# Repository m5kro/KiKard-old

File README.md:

# KiKard-old
KiKard is a non working attempt at creating an NFC testing device. This repo is just here as an example for what not to do.<br>
<br>
There will be a v2 of the project where I fix my mistakes, lower the costs, and make some general improvements.<br>
<br>
Here's a medium article explaining what went wrong: [Here](https://medium.com/the-first-digit/challenges-of-designing-hardware-910d764eaf81)

# Images
Here's what it looks like:<br>

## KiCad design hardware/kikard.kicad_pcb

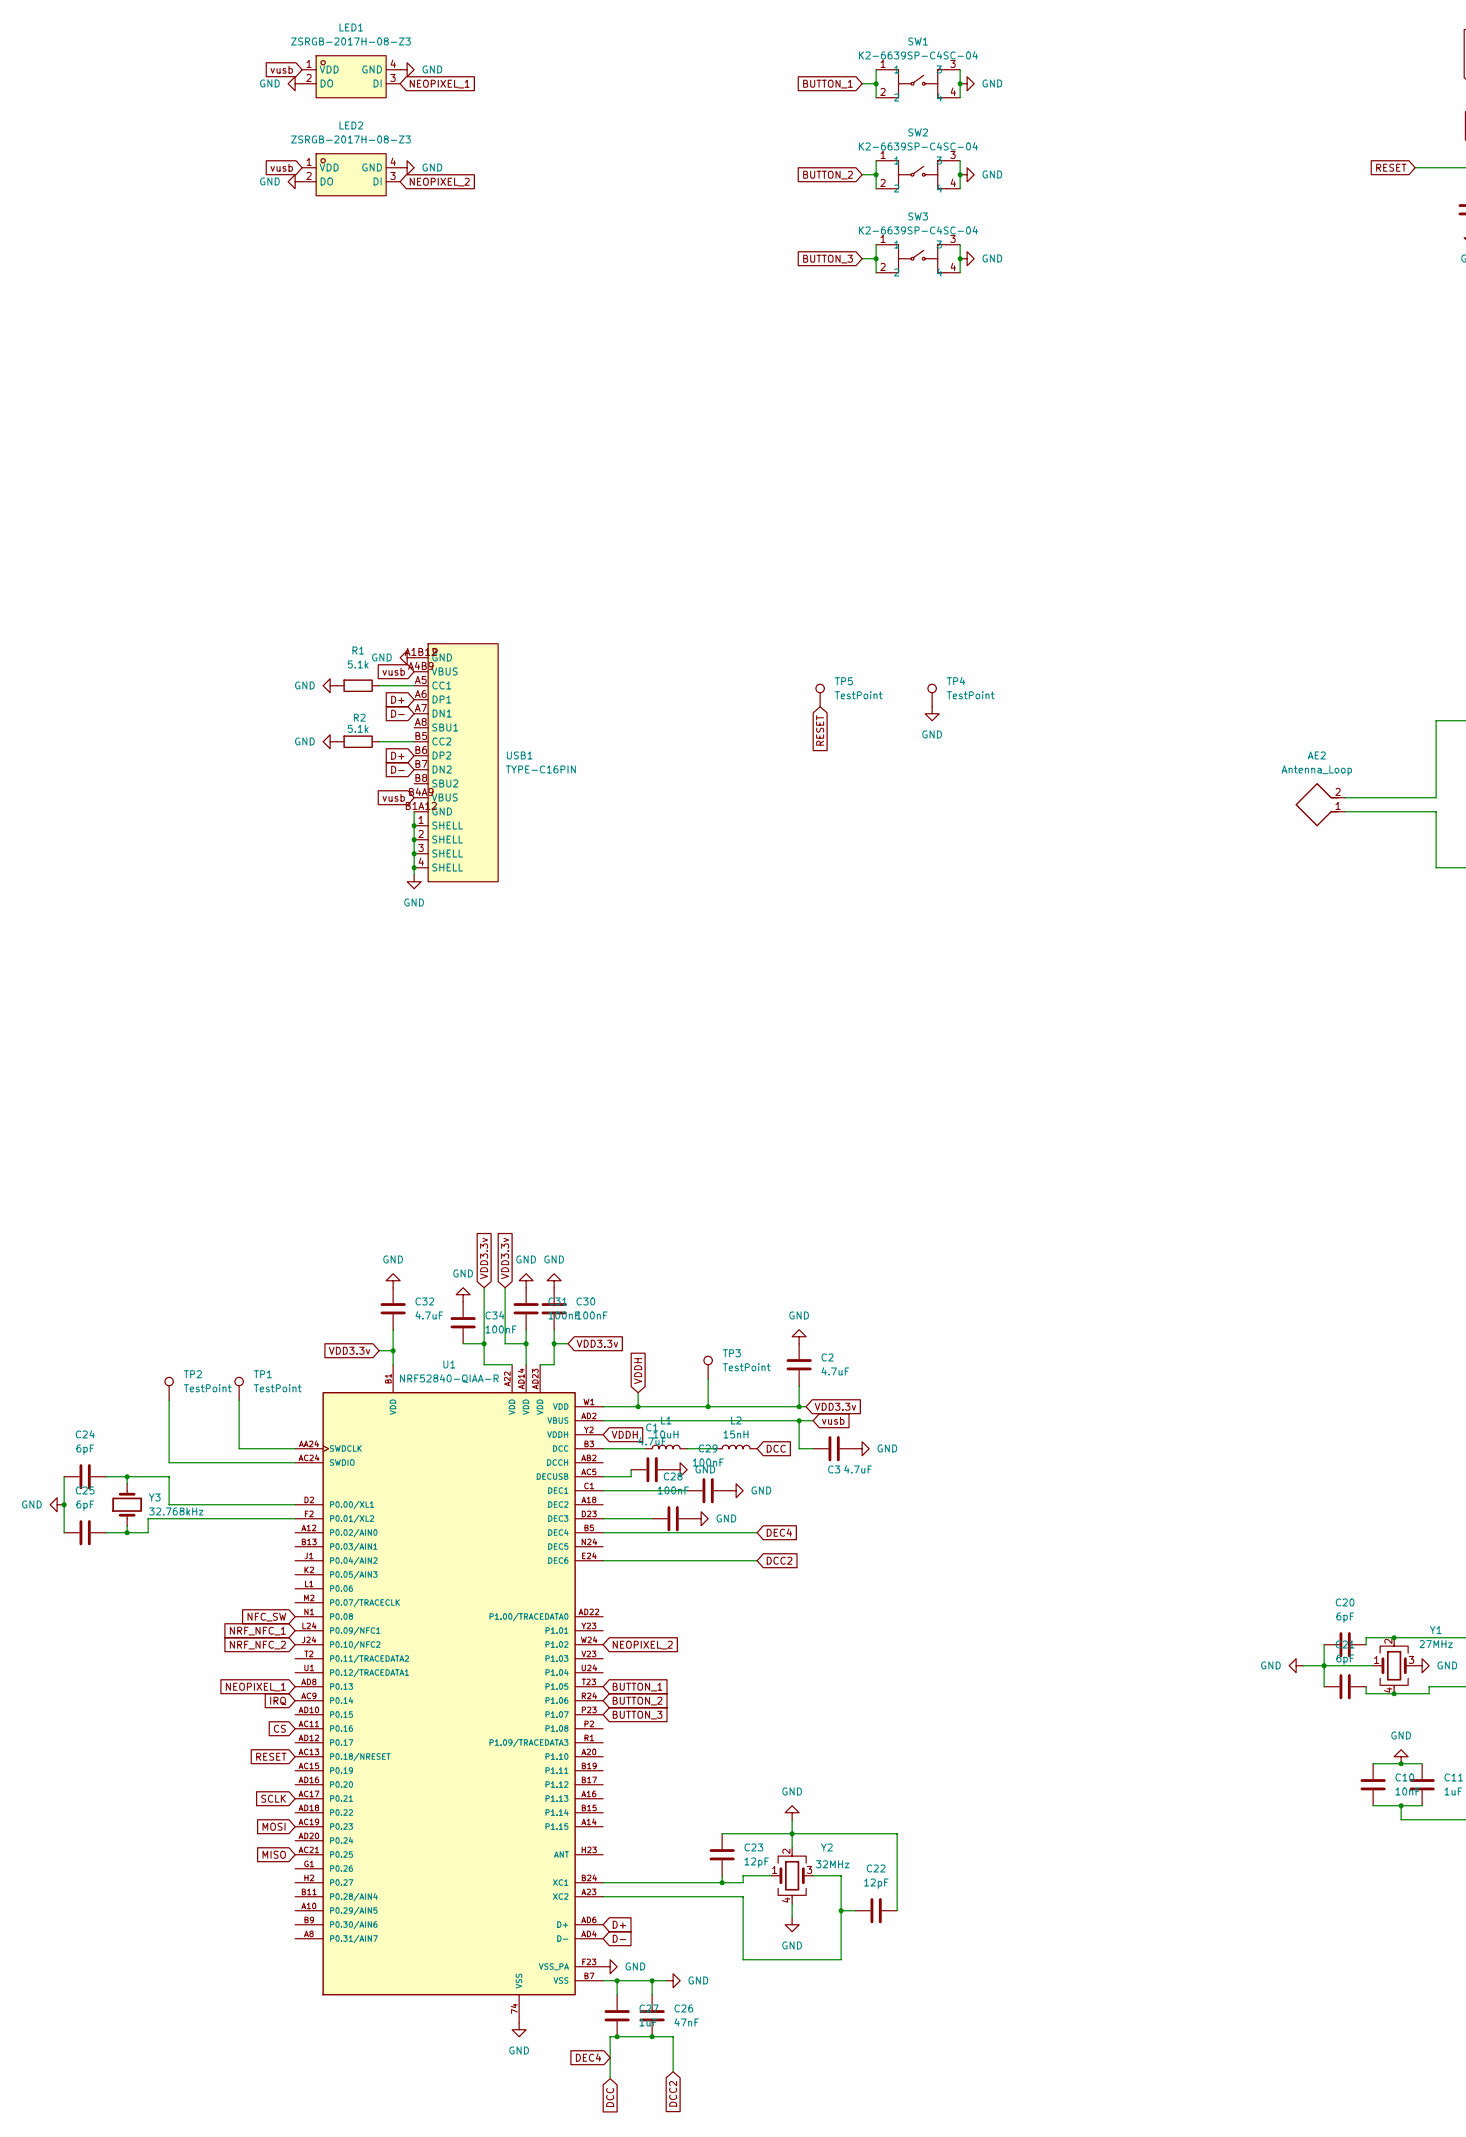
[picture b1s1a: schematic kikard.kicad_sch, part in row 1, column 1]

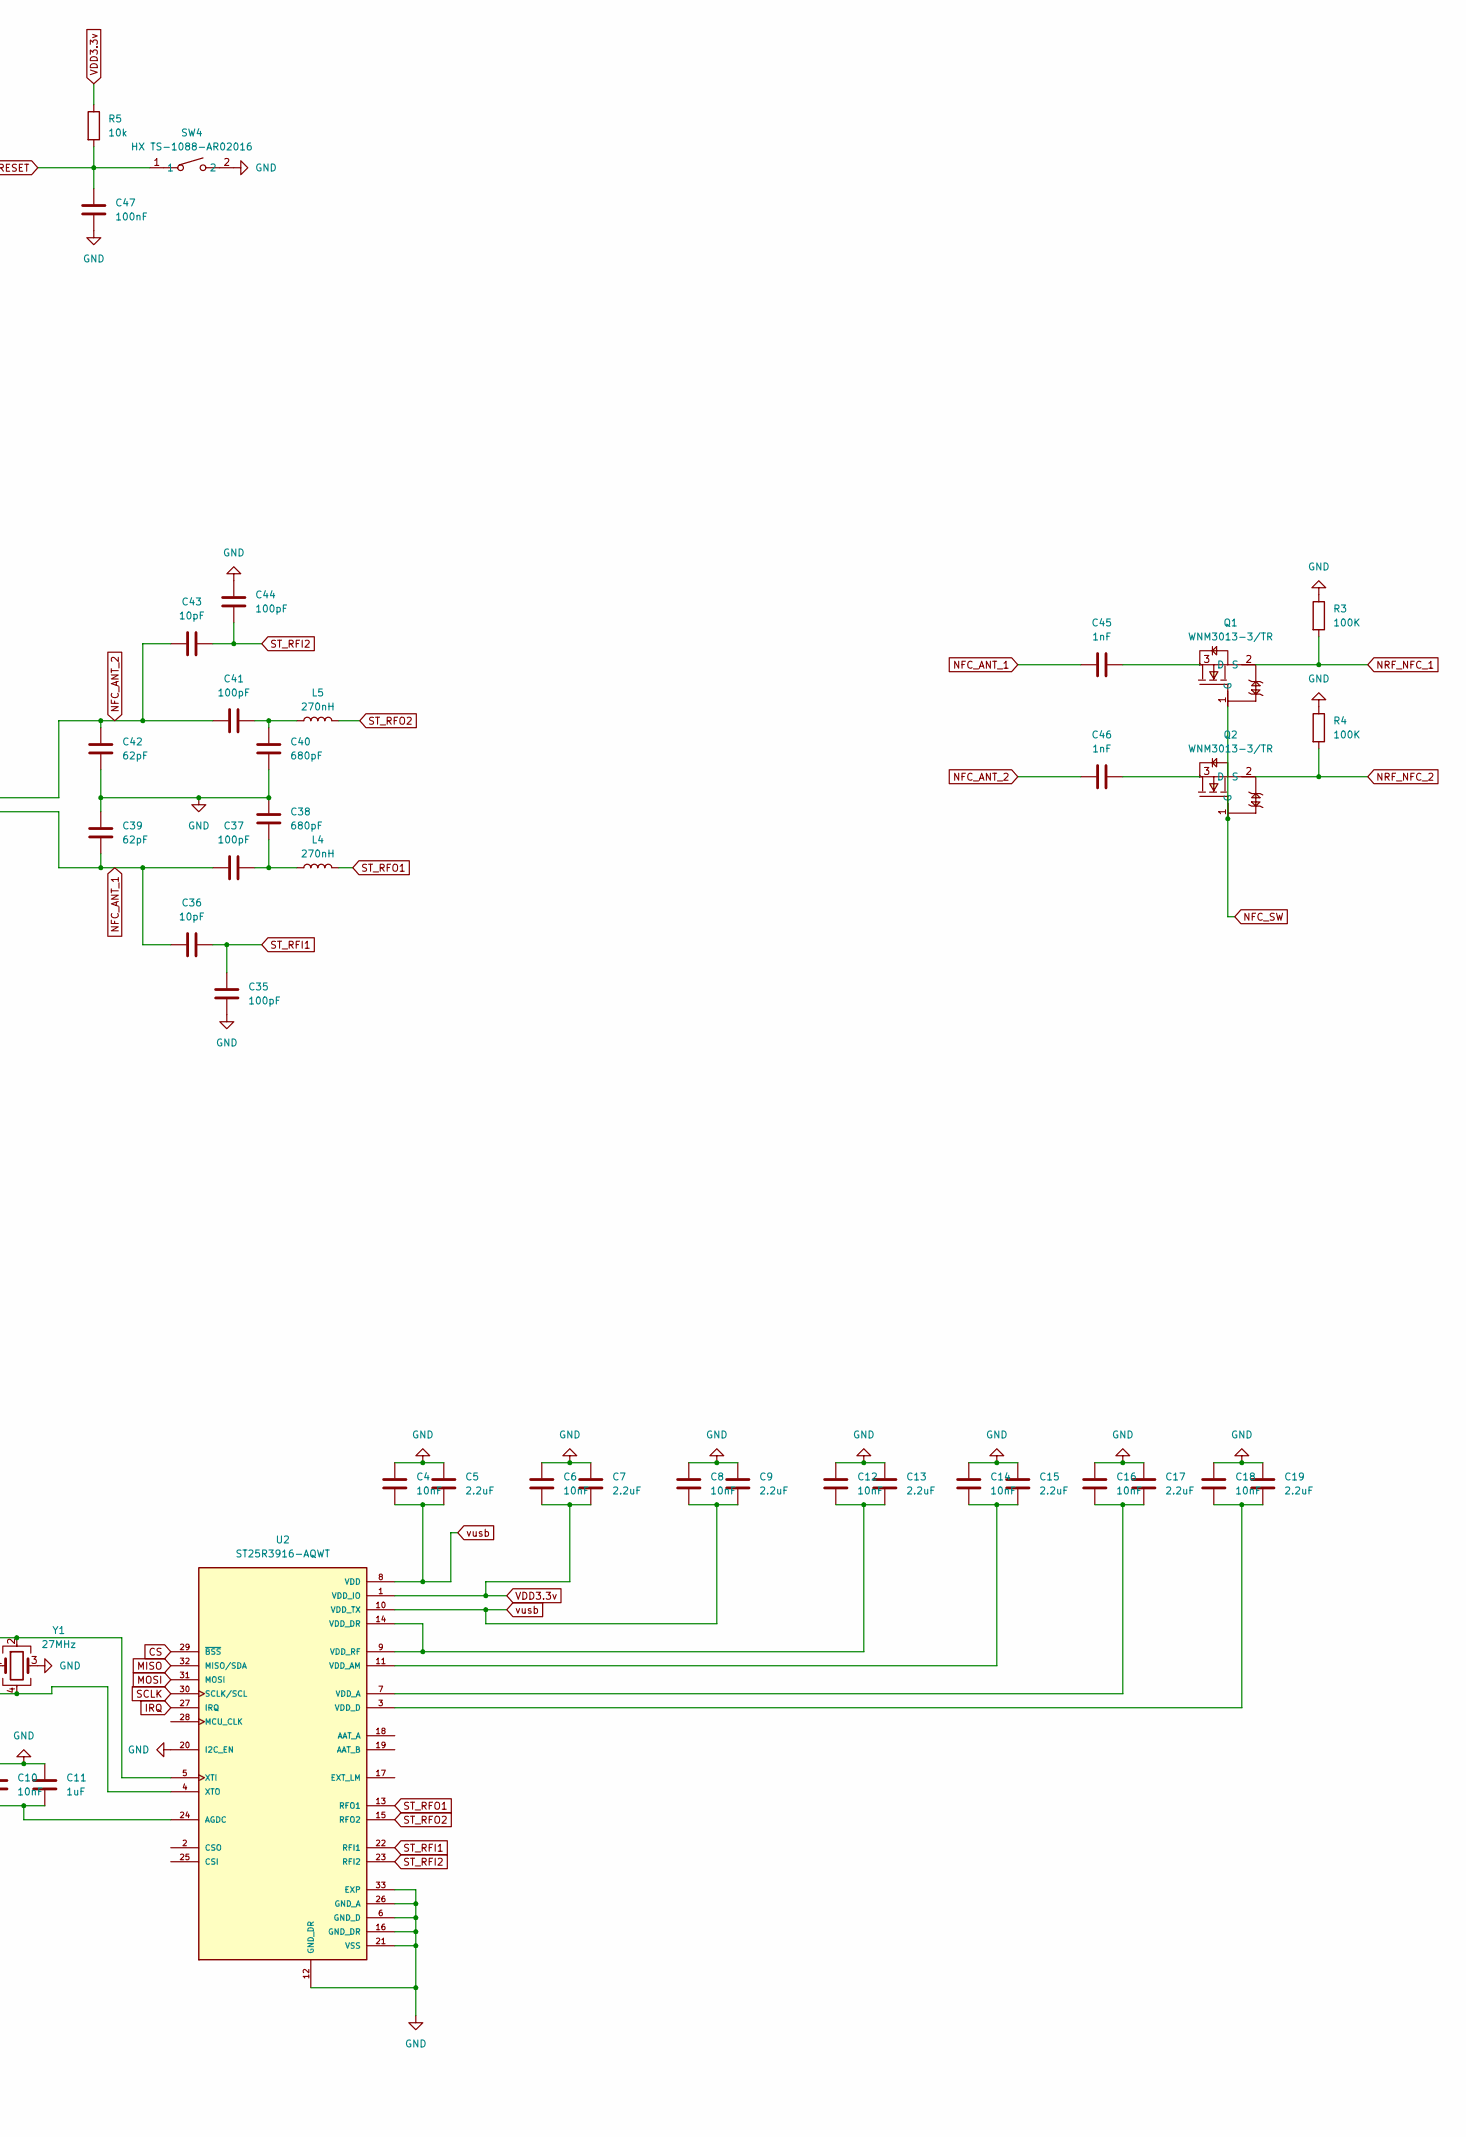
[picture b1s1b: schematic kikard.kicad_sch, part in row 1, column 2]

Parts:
AE2: Antenna_Loop; kikard-ant-v1.0
C1, C2, C3, C32: 4.7uF; C0603
C4, C6, C8, C10, C12, C14, C16, C18: 10nF; C0402
C5, C7, C9, C13, C15, C17, C19: 2.2uF; C0603
C11, C27: 1uF; C0402
C20, C21, C24, C25: 6pF; C0402
C22, C23: 12pF; C0402
C26: 47nF; C0402
C28, C29, C30, C31, C34, C47: 100nF; C0402
C35, C37, C41, C44: 100pF; C0402
C36, C43: 10pF; C0402
C38, C40: 680pF; C0402
C39, C42: 62pF; C0402
C45, C46: 1nF; C0402
L1: 10uH; L0603
L2: 15nH; L0603
L4, L5: 270nH; L0402
LED1, LED2: ZSRGB-2017H-08-Z3; LED-SMD_4P-L2.0-W1.8-P0.90_XGM-S0807RGB; LCSC Part C7497245
Q1, Q2: WNM3013-3/TR; SOT-723_L1.2-W0.8-P0.40-LS1.2-BR; LCSC Part C239659
R1, R2: 5.1k; R0402
R3, R4: 100K; R0603
R5: 10k; R0402
SW1, SW2, SW3: K2-6639SP-C4SC-04; KEY-SMD_4P-L6.0-W6.0-P3.90-LS9.0; LCSC Part C83206
SW4: HX TS-1088-AR02016; SW-SMD_L4.0-W2.9-LS5.0; LCSC Part C36498961
TP1, TP2, TP3, TP4, TP5: TestPoint; TestPoint_Pad_D1.0mm
U1: NRF52840-QIAA-R; XCVR_NRF52840-QIAA-R; PARTREV v1.1
U2: ST25R3916-AQWT; QFN50P500X500X100-33N; PARTREV 4
USB1: TYPE-C16PIN; USB-C-SMD_TYPE-C16PIN; LCSC Part C393939
Y1: 27MHz; CRYSTAL-SMD_4P-L2.0-W1.6-BL-B
Y2: 32MHz; CRYSTAL-SMD_4P-L2.0-W1.6-BL-2
Y3: 32.768kHz; OSC-SMD_L1.6-W1.0

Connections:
BUTTON_1: SW1.1, SW1.2, U1.T23 (P1.05)
BUTTON_2: SW2.1, SW2.2, U1.R24 (P1.06)
BUTTON_3: SW3.1, SW3.2, U1.P23 (P1.07)
CS: U1.AC11 (P0.16), U2.29 (~BSS)
D+: U1.AD6 (D+), USB1.A6 (DP1), USB1.B6 (DP2)
D-: U1.AD4 (D-), USB1.A7 (DN1), USB1.B7 (DN2)
DCC: C26.2, C27.2, L2.2, U1.B5 (DEC4), U1.E24 (DEC6)
GND: C1.1, C2.1, C3.2, C4.1, C5.1, C6.1, C7.1, C8.1, C9.1, C10.1, C11.1, C12.1, C13.1, C14.1, C15.1, C16.1, C17.1, C18.1, C19.1, C20.1, C21.1, C22.2, C23.2, C24.1, C25.1, C26.1, C27.1, C28.2, C29.2, C30.1, C31.1, C32.1, C34.1, C35.2, C38.1, C39.1, C40.2, C42.2, C44.1, C47.2, LED1.2 (DO), LED1.4 (GND), LED2.2 (DO), LED2.4 (GND), R1.2, R2.2, R3.1, R4.1, SW1.3, SW1.4, SW2.3, SW2.4, SW3.3, SW3.4, SW4.2, TP4.1, U1.74 (VSS), U1.B7 (VSS), U1.F23 (VSS_PA), U2.6 (GND_D), U2.12 (GND_DR), U2.16 (GND_DR), U2.20 (I2C_EN), U2.21 (VSS), U2.26 (GND_A), U2.33 (EXP), USB1.1 (SHELL), USB1.2 (SHELL), USB1.3 (SHELL), USB1.4 (SHELL), USB1.A1B12 (GND), USB1.B1A12 (GND), Y1.1, Y1.3, Y2.2, Y2.4
IRQ: U1.AC9 (P0.14), U2.27 (IRQ)
MISO: U1.AC21 (P0.25), U2.32 (MISO/SDA)
MOSI: U1.AC19 (P0.23), U2.31 (MOSI)
NEOPIXEL_1: LED1.3 (DI), U1.AD8 (P0.13)
NEOPIXEL_2: LED2.3 (DI), U1.W24 (P1.02)
NFC_ANT_1: AE2.1, C36.1, C37.1, C39.2, C45.1
NFC_ANT_2: AE2.2, C41.1, C42.1, C43.1, C46.1
NFC_SW: Q1.1 (G), Q2.1 (G), U1.N1 (P0.08)
NRF_NFC_1: Q1.2 (S), R3.2, U1.L24 (P0.09/NFC1)
NRF_NFC_2: Q2.2 (S), R4.2, U1.J24 (P0.10/NFC2)
unnamed: C37.2, C38.2, L4.1
unnamed: C40.1, C41.2, L5.1
unnamed: L1.2, L2.1
unnamed: C45.2, Q1.3 (D)
unnamed: C46.2, Q2.3 (D)
unnamed: L1.1, U1.B3 (DCC)
unnamed: C29.1, U1.C1 (DEC1)
unnamed: C28.1, U1.D23 (DEC3)
unnamed: C1.2, U1.AC5 (DECUSB)
unnamed: C24.2, U1.D2 (P0.00/XL1), Y3.2
unnamed: C25.2, U1.F2 (P0.01/XL2), Y3.1
unnamed: TP1.1, U1.AA24 (SWDCLK)
unnamed: TP2.1, U1.AC24 (SWDIO)
unnamed: C23.1, U1.B24 (XC1), Y2.1
unnamed: C22.1, U1.A23 (XC2), Y2.3
unnamed: C10.2, C11.2, U2.24 (AGDC)
unnamed: C16.2, C17.2, U2.7 (VDD_A)
unnamed: C14.2, C15.2, U2.11 (VDD_AM)
unnamed: C18.2, C19.2, U2.3 (VDD_D)
unnamed: C12.2, C13.2, U2.9 (VDD_RF), U2.14 (VDD_DR)
unnamed: C20.2, U2.5 (XTI), Y1.2
unnamed: C21.2, U2.4 (XTO), Y1.4
unnamed: R1.1, USB1.A5 (CC1)
unnamed: R2.1, USB1.B5 (CC2)
RESET: C47.1, R5.2, SW4.1, TP5.1, U1.AC13 (P0.18/NRESET)
SCLK: U1.AC17 (P0.21), U2.30 (SCLK/SCL)
ST_RFI1: C35.1, C36.2, U2.22 (RFI1)
ST_RFI2: C43.2, C44.2, U2.23 (RFI2)
ST_RFO1: L4.2, U2.13 (RFO1)
ST_RFO2: L5.2, U2.15 (RFO2)
VDD3.3v: C2.2, C6.2, C7.2, C30.2, C31.2, C32.2, C34.2, R5.1, TP3.1, U1.A22 (VDD), U1.AD14 (VDD), U1.AD23 (VDD), U1.B1 (VDD), U1.W1 (VDD), U1.Y2 (VDDH), U2.1 (VDD_IO)
vusb: C3.1, C4.2, C5.2, C8.2, C9.2, LED1.1 (VDD), LED2.1 (VDD), U1.AD2 (VBUS), U2.8 (VDD), U2.10 (VDD_TX), USB1.A4B9 (VBUS), USB1.B4A9 (VBUS)

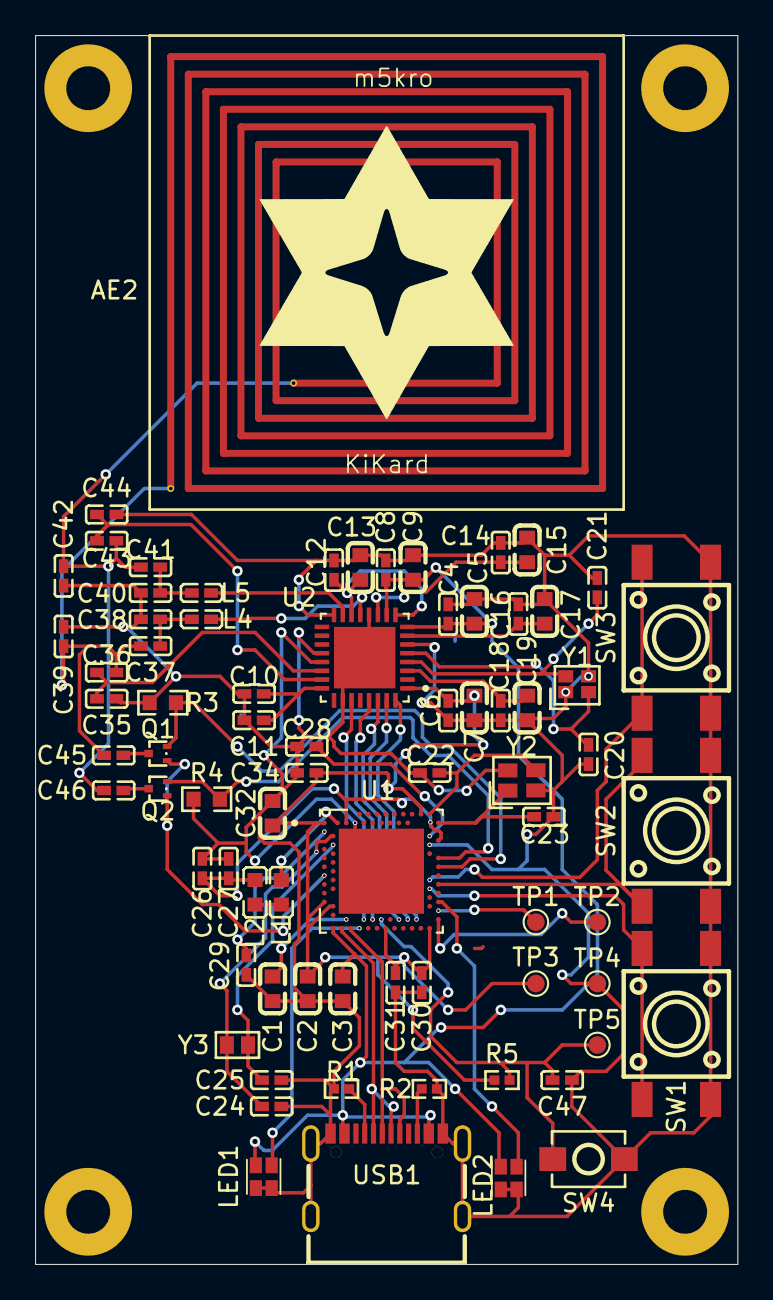
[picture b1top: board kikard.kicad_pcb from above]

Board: 2 copper layers, 40.0 x 70.0 mm, 75 parts (0 on the bottom side), 50 nets.

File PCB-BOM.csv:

"Part","Designator","Quantity","Price per Unit","Total","JLCPCB/LCSC Part No.","Link"
"NRF-52840-QIAA-R","U1","1","4.0290","4.0290","C190794","https://jlcpcb.com/partdetail/NordicSemicon-NRF52840_QIAAR/C190794"
"ST25R3916-AQWT","U2","1","3.3795","3.3795","C2908147","https://jlcpcb.com/partdetail/STMicroelectronics-ST25R3916AQ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"
"WNM3013-3/TR","Q1, Q2","2","0.0333","0.0667","C239659","https://jlcpcb.com/partdetail/WILLSEMI_Will_Semicon-WNM3013_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"
"32MHz Crystal Oscillator","Y2","1","0.0890","0.0890","C2682773","https://jlcpcb.com/partdetail/2777870-X201632MOB4SI/C2682773"
"27MHz Crystal Oscillator","Y1","1","0.1773","0.1773","C576558","https://jlcpcb.com/partdetail/604049-XRCGB27M120F3M00R0/C576558"
"32KHz Crystal Oscillator","Y3","1","0.3825","0.3825","C383847","https://jlcpcb.com/partdetail/357119-X161032768KGD2SI/C383847"
"USB-C Port","USB1","1","0.0642","0.0642","C393939","https://jlcpcb.com/partdetail/SHOUHAN-TYPEC16PIN/C393939"
"RGBLED","LED1, LED2","2","0.0807","0.1614","C7497245","https://jlcpcb.com/partdetail/ChauLight-ZSRGB_2017H_08Z3/C7497245"
"Button","SW1, SW2, SW3","3","0.0380","0.1140","C83206","https://jlcpcb.com/partdetail/Korean_HropartsElec-K2_6639SP_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"
"Small Button","SW4","1","0.0299","0.0299","C36498961","https://jlcpcb.com/partdetail/hanxia-HX_3x4x2_2P_25N/C36498961"
"100k Ohm Resistor","R3, R4","2","0.0010","0.0020","C14675","https://jlcpcb.com/partdetail/YAGEO-RC0603FR07100KL/C14675"
"10k Ohm Resistor","R5","1","0.0004","0.0004","C25531","https://jlcpcb.com/partdetail/26274-0402WGJ0103TCE/C25531"
"5.1k Ohm Resistor","R1, R2","2","0.0004","0.0008","C25941","https://jlcpcb.com/partdetail/26684-0402WGJ0512TCE/C25941"
"4.7uF Capacitor","C1, C2, C3, C32","4","0.0101","0.0404","C19666","https://jlcpcb.com/partdetail/20375-CL10A475KO8NNNC/C19666"
"2.2uF Capacitor","C5, C7, C9, C13, C15, C17, C19","7","0.0060","0.0420","C1607","https://jlcpcb.com/partdetail/1959-CL10A225KP8NNNC/C1607"
"1uF Capacitor","C11, C27","2","0.0016","0.0032","C14445","https://jlcpcb.com/partdetail/15107-CL05A105KP5NNNC/C14445"
"100nF Capacitor","C28, C29, C30, C31, C34, C47","6","0.0011","0.0066","C56392","https://jlcpcb.com/partdetail/57421-0402B104K250NT/C56392"
"47nF Capacitor","C26","1","0.0017","0.0017","C82219","https://jlcpcb.com/partdetail/83376-0402B473K500NT/C82219"
"10nF Capacitor","C4, C6, C8, C10, C12, C14, C16, C18","8","0.0010","0.0080","C1524","https://jlcpcb.com/partdetail/1876-0402B103K500NT/C1524"
"1nF Capacitor","C45, C46","2","0.0089","0.0178","C343059","https://jlcpcb.com/partdetail/TDK-C1005C0G1E102JT000F/C343059"
"680pF Capacitor","C38, C40","2","0.0011","0.0022","C1541","https://jlcpcb.com/partdetail/1893-0402B681K500NT/C1541"
"100pF Capacitor","C35, C37, C41, C44","4","0.0089","0.0356","C1546","https://jlcpcb.com/partdetail/1898-0402CG101J500NT/C1546"
"62pF Capacitor","C39, C42","2","0.0014","0.0028","C281763","https://jlcpcb.com/partdetail/YAGEO-CC0402JRNPO9BN620/C281763"
"12pF Capacitor","C22, C23","2","0.0010","0.0020","C1547","https://jlcpcb.com/partdetail/1899-0402CG120J500NT/C1547"
"10pF Capacitor","C36, C43","2","0.0010","0.0020","C1545","https://jlcpcb.com/partdetail/1897-0402CG100J500NT/C1545"
"6pF Capacitor","C20, C21, C24, C25","4","0.0010","0.0040","C1575","https://jlcpcb.com/partdetail/1927-0402CG6R0C500NT/C1575"
"10uH Inductor","L1","1","0.0212","0.0212","C51942","https://jlcpcb.com/partdetail/Sunlord-MCL1608S100MT/C51942"
"270nH Inductor","L4, L5","2","0.0077","0.0154","C76784","https://jlcpcb.com/partdetail/TDK-MLG1005SR27JT000/C76784"
"15nH Inductor","L2","1","0.0106","0.0106","C23651","https://jlcpcb.com/partdetail/Sunlord-SDCL1608C15NJTDF/C23651"

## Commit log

2025-08-01 whoops
2025-08-01 images
2025-08-24 Update Medium article link in README
